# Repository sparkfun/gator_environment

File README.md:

SparkFun gator:environment - micro:bit Accessory Board 
=============================

[*SparkFun gator:environment - micro:bit Accessory Board  (SEN-15269)*](https://www.sparkfun.com/products/15269)

(Modify Description)
The SparkFun CCS811/BME280 Combo Breakout is perfect for sensing anything you may want to know about the air quality. This breakout will fine tune eCO<sub>2</sub> and tVOC readings from the CCS811 using humidity and temperature readings from the BME280. The breakout will also detect barometric pressure.

Repository Contents
-------------------

* **/Hardware** - Eagle design files (.brd, .sch)
* **/Production** - Production panel files (.brd)

Documentation
--------------

* **[Hookup Guide](https://learn.sparkfun.com/tutorials/sparkfun-gatorenvironment-hookup-guide)** - Basic hookup guide for the gator:environment.
* **[gator:environment PXT Package](https://github.com/sparkfun/pxt-gator-environment)** - PXT- package for the MakeCode gator:environment extension.

License Information
-------------------

This product is _**open source**_! 

Please review the LICENSE.md file for license information. 

If you have any questions or concerns on licensing, please visit the [SparkFun Forum](https://forum.sparkfun.com/index.php) and post a topic. For more general questions related to our gator boards, please visit this section of the forum: [SparkFun Forums: Educational Products](https://forum.sparkfun.com/viewforum.php?f=155)

Distributed as-is; no warranty is given.

- Your friends at SparkFun.

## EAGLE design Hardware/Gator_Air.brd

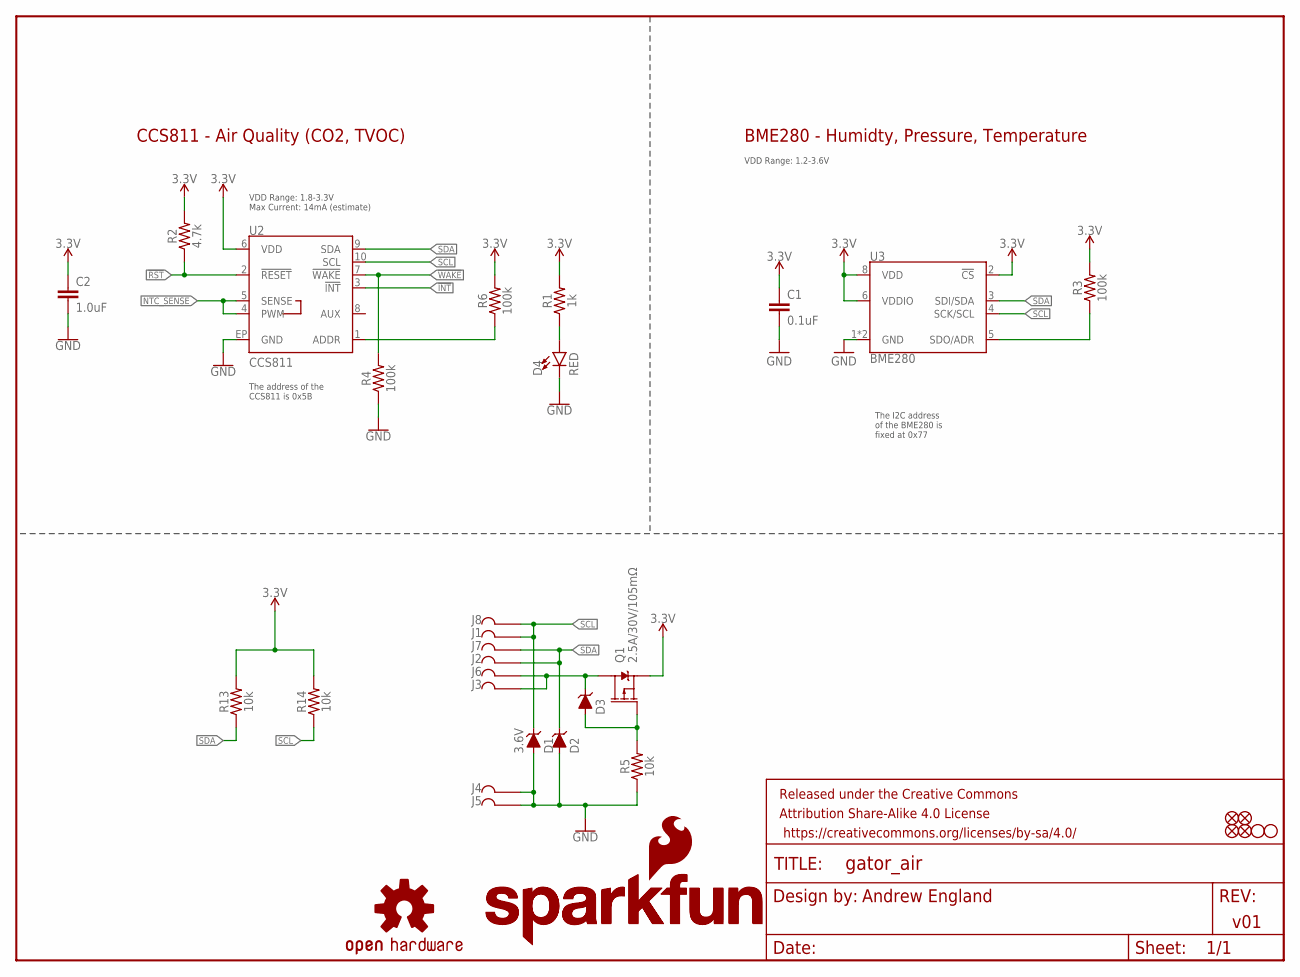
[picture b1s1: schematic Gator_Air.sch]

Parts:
C1: 0.1uF; 0603
C2: 1.0uF; 0603
D1, D2, D3: 3.6V; SOD-323
D4: RED; LED-0603
FD1, FD2, FD3, FD4: FIDUCIAL1X2; FIDUCIAL-1X2
FRAME1: FRAME-LETTER; CREATIVE_COMMONS
H2, H4: STAND-OFF
J1, J2, J3, J4, J5, J6, J7, J8: GATORGATOR_MINI; GATOR_MINI
LOGO1: SFE_LOGO_NAME.1_INCH; SFE_LOGO_NAME_.1
LOGO2: SFE_LOGO_NAME_FLAME.1_INCH; SFE_LOGO_NAME_FLAME_.1
LOGO4: OSHW-LOGOS; OSHW-LOGO-S
Q1: 2.5A/30V/105mΩ; SOT23-3
R1: 1k; 0603
R2: 4.7k; 0603
R3, R4, R6: 100k; 0603
R5, R13, R14: 10k; 0603
U2: CCS811; LGA10
U3: BME280; LGA-8-2.5X2.5

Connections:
3.3V: C1.1, C2.1, Q1.2 (S), R1.2, R2.2, R3.2, R6.2, R13.2, R14.2, U2.6 (VDD), U3.2 (!CS), U3.6 (VDDIO), U3.8 (VDD)
!INT: U2.3 (!INT!)
!RST: R2.1, U2.2 (!RESET!)
!WAKE: R4.2, U2.7 (!WAKE!)
CCS811_ADDR: R6.1, U2.1 (ADDR)
GND: C1.2, C2.2, D1.A, D2.A, D4.C, J4.P$2, J5.P$2, R4.1, R5.1, U2.EP (GND), U3.1 (GND), U3.7 (GND)
unnamed: D4.A, R1.1
unnamed: D3.C, J3.P$2, J6.P$2, Q1.3 (D)
unnamed: D3.A, Q1.1 (G), R5.2
NTC_SENSE: U2.4 (PWM), U2.5 (SENSE)
SCL: D1.C, J1.P$2, J8.P$2, R14.1, U2.10 (SCL), U3.4 (SCK/SCL)
SDA: D2.C, J2.P$2, J7.P$2, R13.1, U2.9 (SDA), U3.3 (SDI/SDA)
SDO/ADR: R3.1, U3.5 (SDO/ADR)

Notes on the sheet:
VDD Range: 1.8-3.3V Max Current: 14mA (estimate)
CCS811 - Air Quality (CO2, TVOC)
The address of the CCS811 is 0x5B
v01
The I2C address of the BME280 is fixed at 0x77
BME280 - Humidty, Pressure, Temperature
Andrew England
VDD Range: 1.2-3.6V

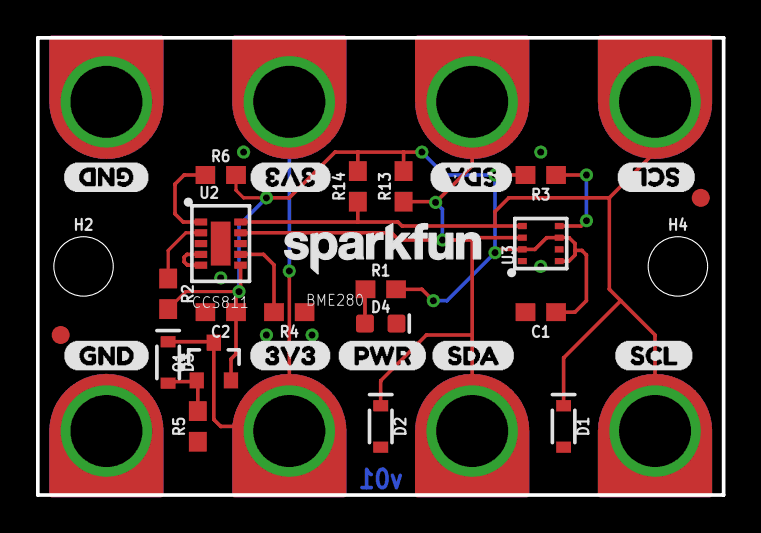
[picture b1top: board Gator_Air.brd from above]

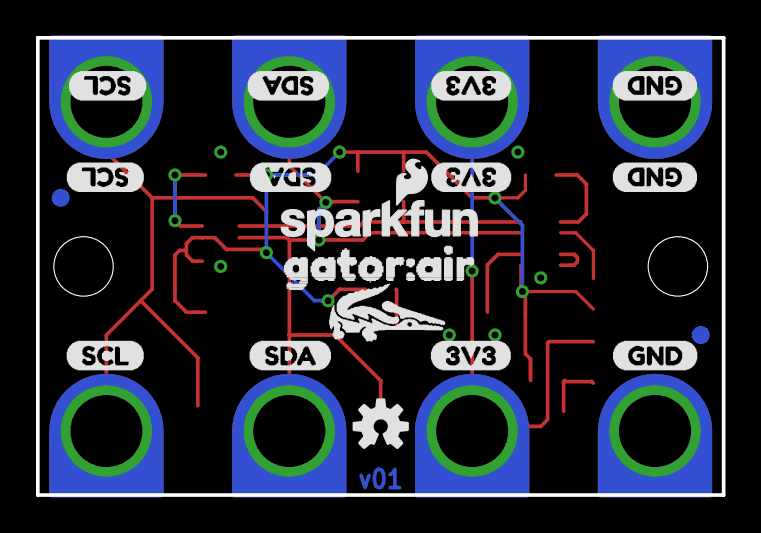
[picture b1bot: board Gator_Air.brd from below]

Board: 2 copper layers, 38.1 x 25.4 mm, 59 parts (18 on the bottom side), 12 nets.

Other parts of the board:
U$1, U$8, U$9, U$16, U$21: 3V33
U$2, U$7, U$10, U$15, U$20: GND0
U$3, U$6, U$11, U$14, U$23: SCL2
U$4, U$5, U$12, U$13, U$22: SDA1
U$17: GATOR#AIR0
U$18: PWR0
U$19: GATORBIT_FINAL_FOR_SILK#01#PNG
U$24: ORDERING_INSTRUCTIONS

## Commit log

2019-02-25 inital layout complete, needs silk and double check
2019-02-25 resizing board, adding silk
2019-02-27 finalizing layout/silk
2019-02-28 adding protection diodes
2019-02-28 finalizing silk
2019-03-01 engineer run of checklist, post review
2019-03-01 pushing unsaved changes from checklist
2019-03-12 post checklist changes
2019-04-16 pre-design review
2019-04-19 engineer run of checklist
2019-04-19 updating pwrsilk
2019-04-22 QC Double check changes
2019-06-12 Update to current product information
    Will need to update forum link and description
2019-06-12 Update
    Troubleshooting link and product description
2019-06-14 cleaning repo

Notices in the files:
parts and their libraries:
SparkFun-Aesthetics: Licensing: Creative Commons ShareAlike 4.0 International - https://creativecommons.org/licenses/by-sa/4.0
SparkFun-Aesthetics: Released under the Creative Commons Attribution Share-Alike 4.0 License
SparkFun-Aesthetics: https://creativecommons.org/licenses/by-sa/4.0
